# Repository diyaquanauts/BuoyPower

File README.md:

# Buoy Power Manager
This project was created 
with KiCAD, and acts a power monitor, power timer, and voltage regulator for the 
raspberry pi.  
Boards can be assembled by JLCPCB for about $50 per set of 5. See the assembled photos below.
### Board Front 

### Board Back

# Instructional Video

# Part Alternative
[Witty Pi 4](https://www.uugear.com/product/witty-pi-4/)

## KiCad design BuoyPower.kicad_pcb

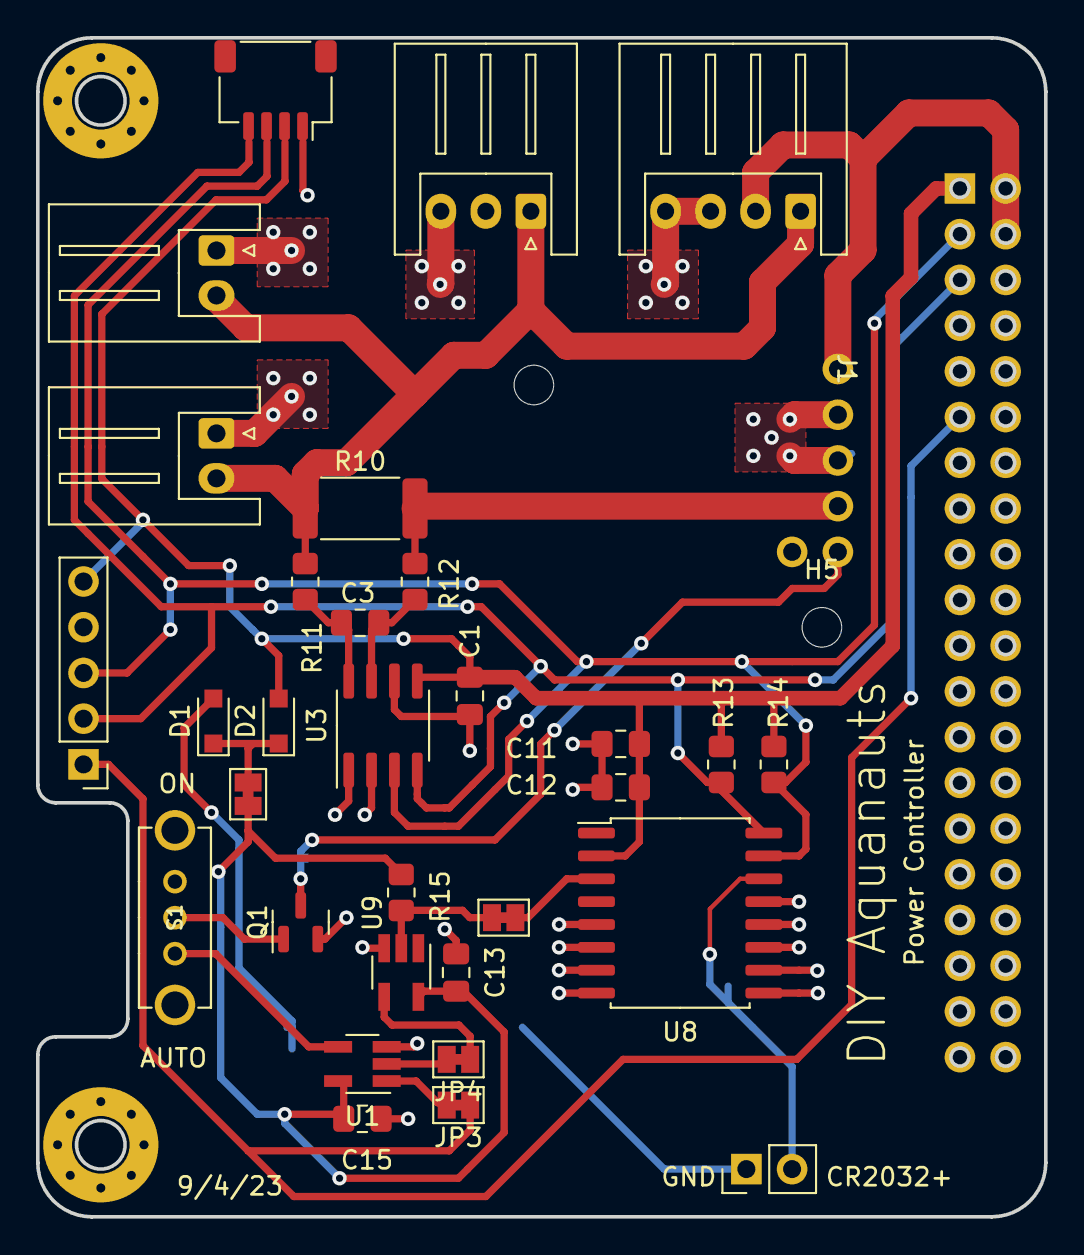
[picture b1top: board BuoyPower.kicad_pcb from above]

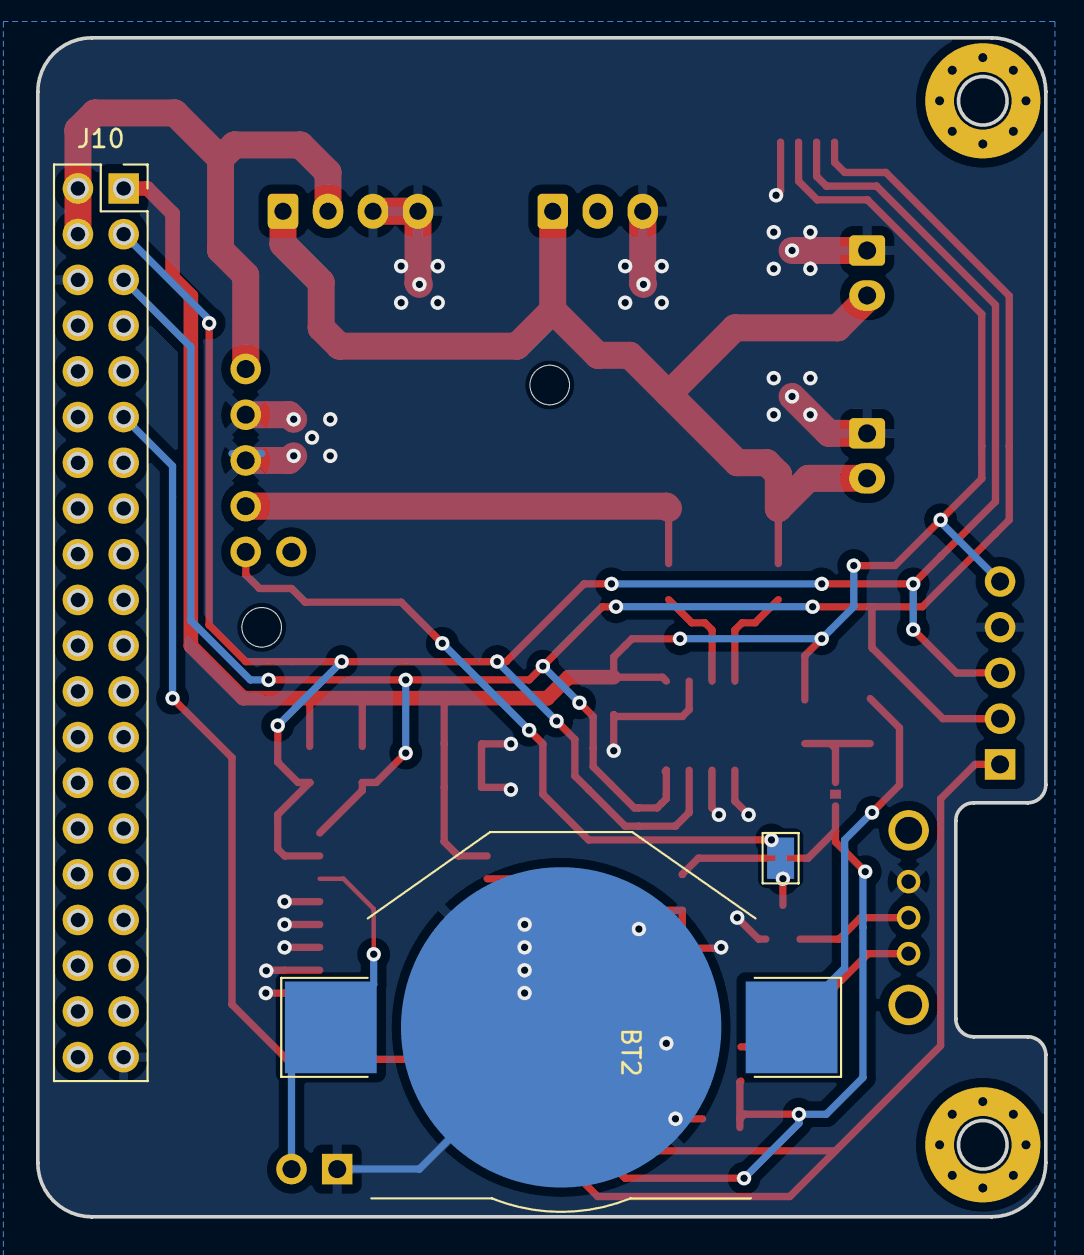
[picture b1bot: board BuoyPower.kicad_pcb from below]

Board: 2 copper layers, 56.0 x 65.5 mm, 39 parts (3 on the bottom side), 21 nets.

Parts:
BT2: Battery_Cell; BatteryHolder_Keystone_3002_1x2032
C1, C3, C12, C13, C15: 0.1uF; C_0805_2012Metric_Pad1.18x1.45mm_HandSolder
C11: 10uF; C_0805_2012Metric_Pad1.18x1.45mm_HandSolder
D1, D2: BAT20J; D_SOD-323_HandSoldering
H1, H5: MountingHole; MountingHole_2.2mm_M2
H2, H3: MountingHole; MountingHole_3.2mm_M3_Pad_Via
J1: Pololu-3782
J2: Conn_01x05; PinHeader_1x05_P2.54mm_Vertical
J4, J7: Conn_01x02_Male; JST_XH_S2B-XH-A_1x02_P2.50mm_Horizontal
J5: Conn_01x03; JST_XH_S3B-XH-A_1x03_P2.50mm_Horizontal
J6: Conn_01x04; JST_SH_SM04B-SRSS-TB_1x04-1MP_P1.00mm_Horizontal
J8: Conn_01x04; JST_XH_S4B-XH-A_1x04_P2.50mm_Horizontal
J9: Conn_01x02_Male; PinHeader_1x02_P2.54mm_Vertical
J10: Conn_02x20_Odd_Even; PinSocket_2x20_P2.54mm_Vertical
JP1, JP42, JP42#2: SolderJumper_2_Bridged; SolderJumper-2_P1.3mm_Bridged_Pad1.0x1.5mm
JP3, JP4: SolderJumper_2_Open; SolderJumper-2_P1.3mm_Bridged_Pad1.0x1.5mm
Q1: IRLML2502; SOT-23
R10: 0.15; R_2512_6332Metric_Pad1.40x3.35mm_HandSolder
R11, R12: 10; R_0805_2012Metric_Pad1.20x1.40mm_HandSolder
R13, R14: 10k; R_0805_2012Metric_Pad1.20x1.40mm_HandSolder
R15: 470k; R_0805_2012Metric_Pad1.20x1.40mm_HandSolder
S1: EG1213; SW_EG1213
U1: 74AHC1G02; SOT-23-5_HandSoldering
U3: INA219AxD; SOIC-8_3.9x4.9mm_P1.27mm
U8: DS3231M; SOIC-16W_7.5x10.3mm_P1.27mm
U9: 74AHC1GU04; SOT-23-5_HandSoldering

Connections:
+5V: J1.1, J8.2, J10.2, J10.4
/HOLD: J2.1, J10.11, JP3.1 (A)
/PowerMonitor/VOUT: J1.4, R10.2, R12.1
/PowerTimer/INT: JP42.2 (B), R15.2, U9.2
/PowerTimer/NINT: JP4.1 (A), U9.4
/REG_EN: J1.5, Q1.3 (D)
/SCL: J2.2, J6.4, J10.5, R13.1, U3.4 (SCL), U8.16 (SCL)
/SDA: J2.3, J6.3, J10.3, R14.1, U3.3 (SDA), U8.15 (SDA)
BATT_IN: J4.2, J5.1, J7.2, J8.1, R10.1, R11.1
GND: BT2.2 (-), C1.1, C11.2, C12.2, C13.1, C15.1, J1.2, J1.3, J2.4, J4.1, J5.3, J6.1, J7.1, J8.3, J8.4, J9.1, J10.6, J10.39, Q1.2 (S), S1.1, U1.3 (GND), U3.1 (A1), U3.2 (A0), U3.6 (GND), U8.5 (GND), U8.6 (GND), U8.7 (GND), U8.8 (GND), U8.9 (GND), U8.10 (GND), U8.11 (GND), U8.12 (GND), U8.13 (GND), U9.3 (GND)
unnamed: BT2.1 (+), D1.2 (A), J9.2, U8.14 (VBAT)
unnamed: D1.1 (K), D2.1 (K), JP1.1 (A)
unnamed: JP3.2 (B), U1.1
unnamed: JP4.2 (B), U1.2
unnamed: JP42.1 (A), U8.3 (~INT/SQW)
unnamed: Q1.1 (G), S1.2
unnamed: S1.3, U1.4
unnamed: C3.2, R11.2, U3.8 (IN+)
unnamed: C3.1, R12.2, U3.7 (IN-)
VBUS: C1.2, C11.1, C12.1, D2.2 (A), J2.5, J6.2, J10.1, R13.2, R14.2, U3.5 (VS), U8.2 (VCC)
VCC: C13.2, C15.2, JP1.2 (B), R15.1, U1.5 (VCC), U9.5 (VCC)

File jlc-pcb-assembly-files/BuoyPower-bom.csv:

Reference,Value,Footprint,Mfr 1,Mfr 1 PN,Supplier 1 Link,Qty
BT2,Battery_Cell,Battery:BatteryHolder_Keystone_3002_1x2032,Keystone Electronics,3002TR,https://www.digikey.com/en/products/detail/keystone-electron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,1
"C2, C11",10uF,Capacitor_SMD:C_0805_2012Metric_Pad1.18x1.45mm_HandSolder,Samsung Electro-Mechanics,CL21A106KOCLRNC,https://www.digikey.com/en/products/detail/samsung-electro-m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,2
"C1, C3, C12, C13, C15",0.1uF,Capacitor_SMD:C_0805_2012Metric_Pad1.18x1.45mm_HandSolder,YAGEO,CC0805KRX7R9BB104,https://www.digikey.com/en/products/detail/yageo/CC0805KRX7R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,5
"D1, D2",BAT20J,Diode_SMD:D_SOD-323_HandSoldering,STMicroelectronics,BAT20JFILM,https://www.digikey.com/en/products/detail/stmicroelectronic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,2
"H2, H3",MountingHole,MountingHole:MountingHole_3.2mm_M3_Pad_Via,NA,NA,NA,2
J1,Pololu-3782,ADAFRUIT_QT_PY:Pololu-3782,Pololu,3782,https://www.pololu.com/product/3782,1
J2,Conn_01x05,Connector_PinHeader_2.54mm:PinHeader_1x05_P2.54mm_Vertical,NA,NA,NA,1
J5,Conn_01x03,Connector_JST:JST_XH_S3B-XH-A_1x03_P2.50mm_Horizontal,NA,NA,NA,1
J6,Conn_01x04,Connector_JST:JST_SH_SM04B-SRSS-TB_1x04-1MP_P1.00mm_Horizontal,JST Sales America Inc.,SM04B-SRSS-TB,https://www.digikey.com/en/products/detail/jst-sales-america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,1
"J4, J7",Conn_01x02_Male,Connector_JST:JST_XH_S2B-XH-A_1x02_P2.50mm_Horizontal,NA,NA,NA,2
J8,Conn_01x04,Connector_JST:JST_XH_S4B-XH-A_1x04_P2.50mm_Horizontal,NA,NA,NA,1
J9,Conn_01x02_Male,Connector_PinHeader_2.54mm:PinHeader_1x02_P2.54mm_Vertical,NA,NA,NA,1
J10,Conn_02x20_Odd_Even,Connector_PinSocket_2.54mm:PinSocket_2x20_P2.54mm_Vertical,Oupiin,2047-2X20G00S3U,https://www.digikey.com/en/products/detail/oupiin/2047-2X20G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,1
JP2-JP4,SolderJumper_2_Open,Jumper:SolderJumper-2_P1.3mm_Open_Pad1.0x1.5mm,NA,NA,NA,3
"JP1, JP42",SolderJumper_2_Bridged,Jumper:SolderJumper-2_P1.3mm_Bridged_Pad1.0x1.5mm,NA,NA,NA,2
R1,120k,Resistor_SMD:R_0805_2012Metric_Pad1.20x1.40mm_HandSolder,"KOA Speer Electronics, Inc.",RK73H2ATTD1203F,https://www.digikey.com/en/products/detail/koa-speer-electro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,1
R10,0.15,Resistor_SMD:R_2512_6332Metric_Pad1.40x3.35mm_HandSolder,Stackpole Electronics Inc,RMCF2512FTR150,https://www.digikey.com/en/products/detail/stackpole-electro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,1
"R11, R12",10,Resistor_SMD:R_0805_2012Metric_Pad1.20x1.40mm_HandSolder,YAGEO,RC0805FR-0710RL,https://www.digikey.com/en/products/detail/yageo/RC0805FR-07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,2
"R13, R14",10k,Resistor_SMD:R_0805_2012Metric_Pad1.20x1.40mm_HandSolder,Stackpole Electronics Inc,RNCP0805FTD10K0,https://www.digikey.com/en/products/detail/stackpole-electro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,2
R15,470k,Resistor_SMD:R_0805_2012Metric_Pad1.20x1.40mm_HandSolder,Stackpole Electronics Inc,RMCF0805JT470Kf,https://www.digikey.com/en/products/detail/stackpole-electro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,1
S1,EG1213,EG1213:SW_EG1213,E-Switch,EG1213,https://www.digikey.com/en/products/detail/e-switch/EG1213/1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,1
U3,INA219AxD,Package_SO:SOIC-8_3.9x4.9mm_P1.27mm,Texas Instruments,INA219BIDR,https://www.digikey.com/en/products/detail/texas-instruments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,1
U8,DS3231M,Package_SO:SOIC-16W_7.5x10.3mm_P1.27mm,Analog Devices Inc./Maxim Integrated,DS3231M+,https://www.digikey.com/en/products/detail/analog-devices-in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,1
U9,74AHC1GU04,Package_TO_SOT_SMD:SOT-23-5_HandSoldering,Texas Instruments,SN74AHC1GU04DBVR,https://www.digikey.com/en/products/detail/texas-instruments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,1
U11,74AHC1G02,Package_TO_SOT_SMD:SOT-23-5_HandSoldering,Texas Instruments,74AHC1G02,,1
Q1,IRLML2502,,,IRLML2502,,

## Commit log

2023-09-10 Sadly, my first commit
2023-09-11 PiShield!!
2023-09-14 Ready to order.
2023-09-14 Pushing to github
2023-09-14 Testing actions
2023-09-14 Please push
2023-09-14 Not pushing zip backups
2023-09-14 Demo action
2023-09-14 Run action when on squash branch
2023-09-14 Fix tracespace cli install
2023-09-14 Add index.html for GitHub Pages
2023-09-14 Fixed path to json file in pages
2023-09-14 Building images locally
2023-09-15 Dynamically generate website?
2023-09-15 Change default brach
2023-09-15 path issue?
2023-09-15 please
2023-09-15 Add write permissions?
2023-09-22 Post-build updates
2023-09-25 technically ok
2023-09-25 Shit! Chinese new year
2023-09-25 revert to single layer
